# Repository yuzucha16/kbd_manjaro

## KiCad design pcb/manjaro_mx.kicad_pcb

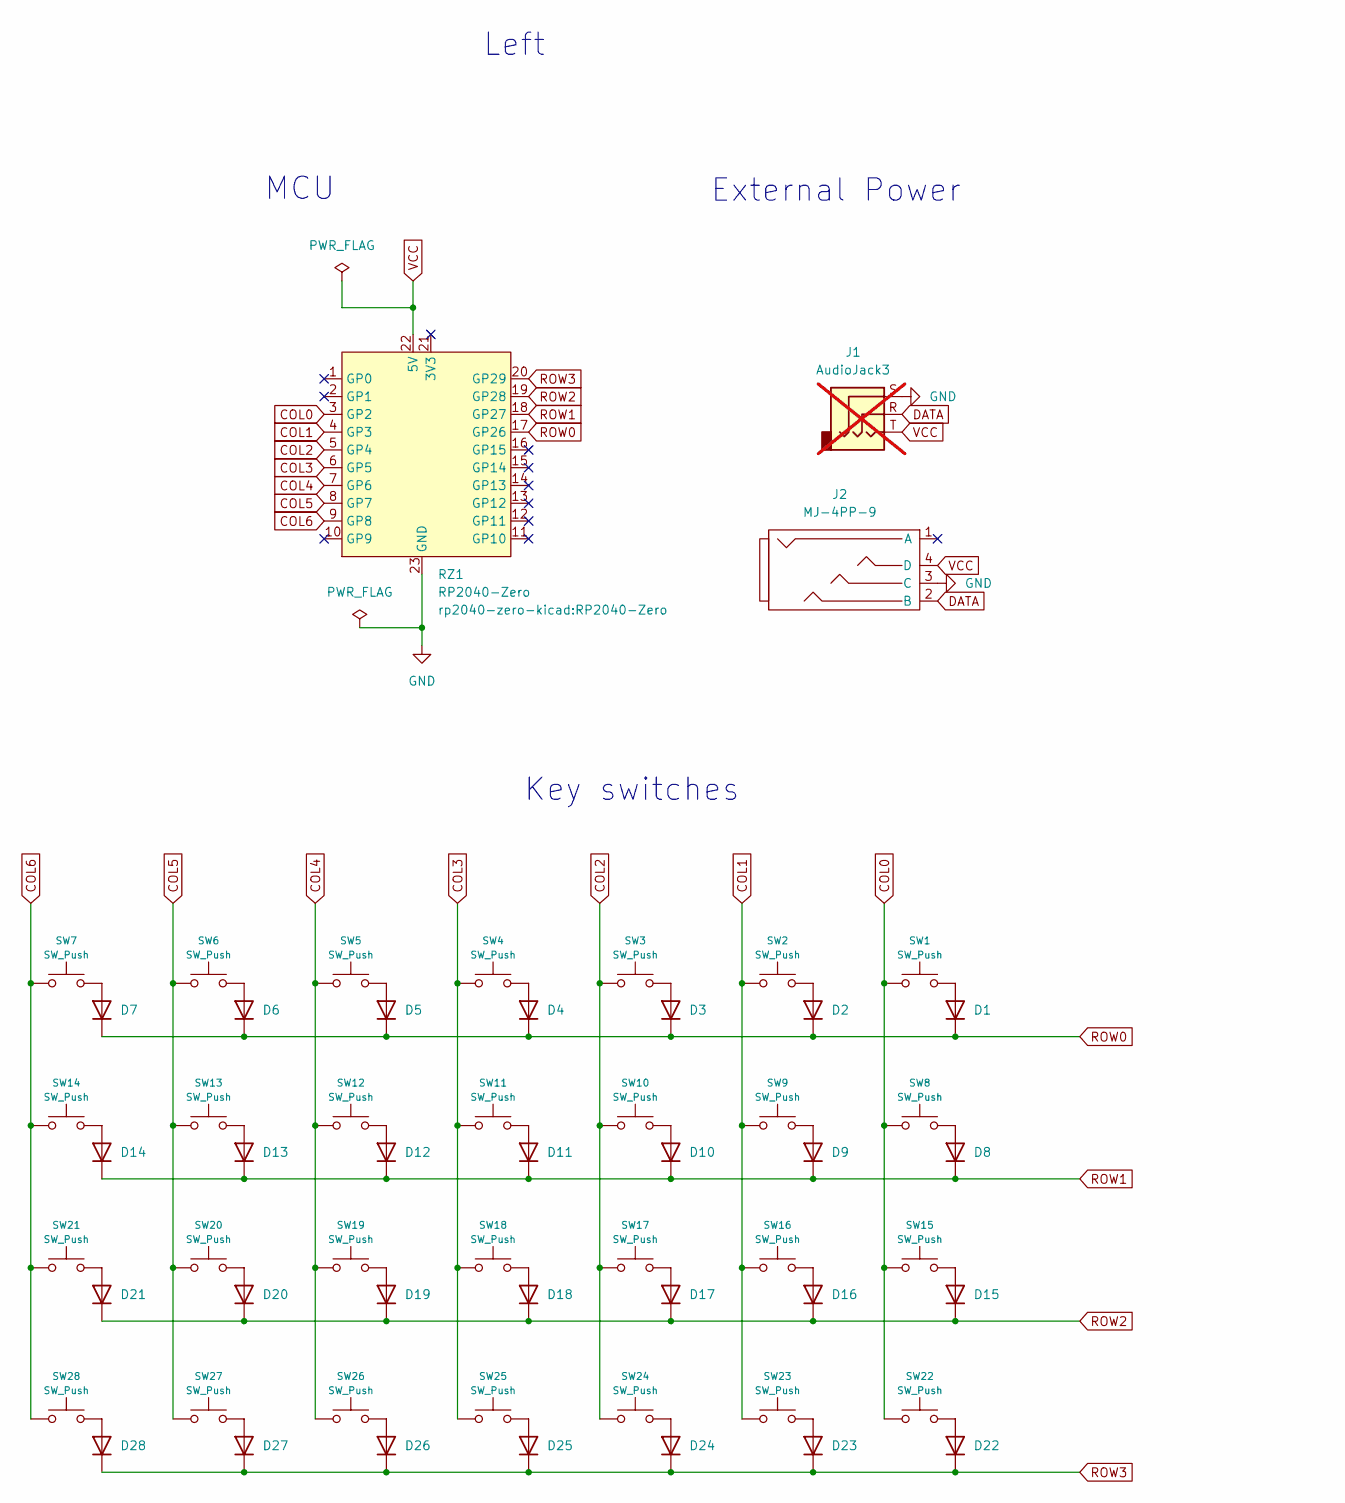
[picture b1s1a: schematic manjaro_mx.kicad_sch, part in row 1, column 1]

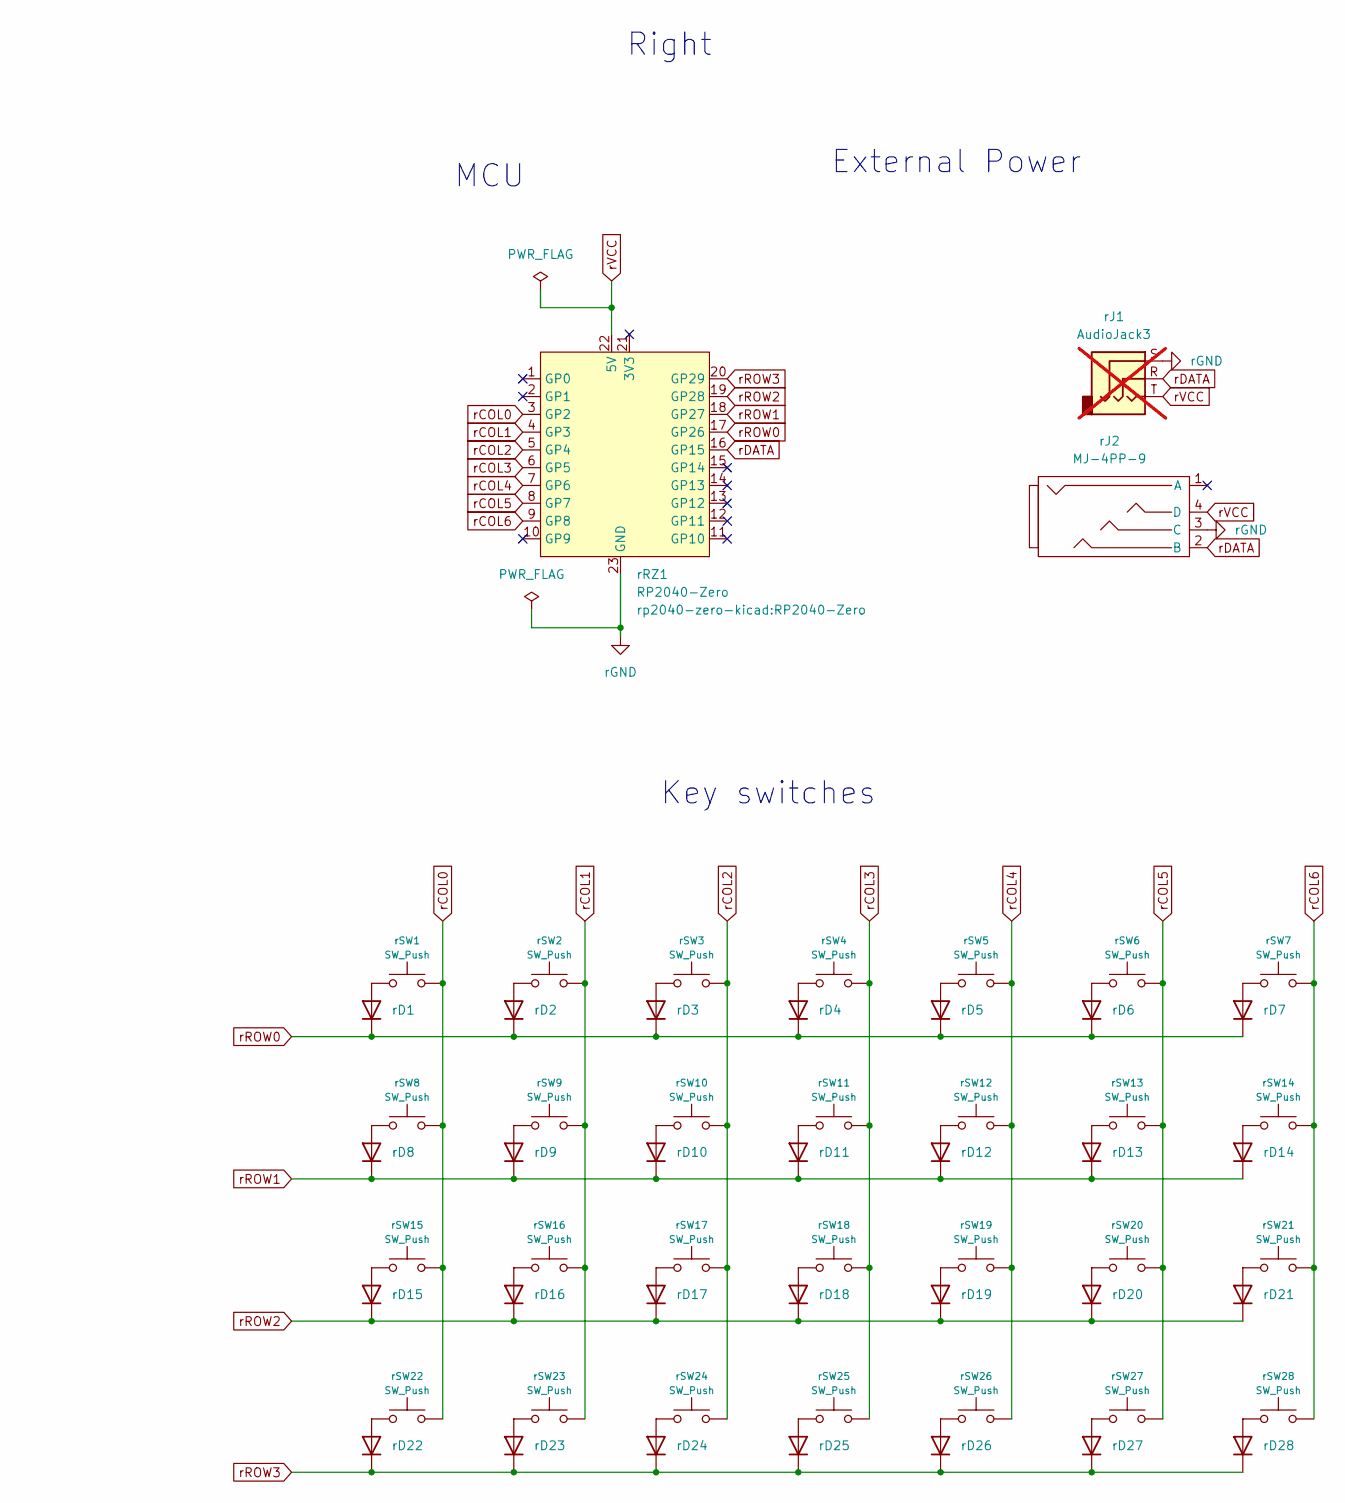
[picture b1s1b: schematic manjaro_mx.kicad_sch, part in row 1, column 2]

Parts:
D1, D2, D3, D4, D5, D6, D7, D8, D9, D10, D11, D12, D13, D14, D15, D16, D17, D18, D19, D20, D21, D22, D23, D24, D25, D26, D27, D28: 1N4148WT; D_SOD-323
J1: AudioJack3; PJ-398A-5A_PJ-399B-6A; not fitted
J2: MJ-4PP-9
RZ1: RP2040-Zero
SW1, SW2, SW3, SW4, SW5, SW6, SW7, SW8, SW9, SW10, SW11, SW12, SW13, SW14, SW15, SW16, SW17, SW18, SW19, SW20, SW21, SW25, SW26, SW27, SW28: SW_Push; keyswitch_cherrymx_hotswap_1u
SW22, SW23, SW24: SW_Push; keyswitch_choc12_hotswap_1u
rD1, rD2, rD3, rD4, rD5, rD6, rD7, rD8, rD9, rD10, rD11, rD12, rD13, rD14, rD15, rD16, rD17, rD18, rD19, rD20, rD21, rD22, rD23, rD24, rD25, rD26, rD27, rD28: 1N4148WT; D_SOD-323
rJ1: AudioJack3; PJ-398A-5A_PJ-399B-6A; not fitted
rJ2: MJ-4PP-9
rRZ1: RP2040-Zero
rSW1, rSW2, rSW3, rSW4, rSW5, rSW6, rSW7, rSW8, rSW9, rSW10, rSW11, rSW12, rSW13, rSW14, rSW15, rSW16, rSW17, rSW18, rSW19, rSW20, rSW21, rSW25, rSW26, rSW27, rSW28: SW_Push; keyswitch_cherrymx_hotswap_1u
rSW22, rSW23, rSW24: SW_Push; keyswitch_choc12_hotswap_1u

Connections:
COL0: RZ1.3 (GP2), SW1.1, SW8.1, SW15.1, SW22.1
COL1: RZ1.4 (GP3), SW2.1, SW9.1, SW16.1, SW23.1
COL2: RZ1.5 (GP4), SW3.1, SW10.1, SW17.1, SW24.1
COL3: RZ1.6 (GP5), SW4.1, SW11.1, SW18.1, SW25.1
COL4: RZ1.7 (GP6), SW5.1, SW12.1, SW19.1, SW26.1
COL5: RZ1.8 (GP7), SW6.1, SW13.1, SW20.1, SW27.1
COL6: RZ1.9 (GP8), SW7.1, SW14.1, SW21.1, SW28.1
DATA: J1.R, J2.2 (B)
GND: J1.S, J2.3 (C), RZ1.23 (GND)
unnamed: D1.2 (A), SW1.2
unnamed: D2.2 (A), SW2.2
unnamed: D3.2 (A), SW3.2
unnamed: D4.2 (A), SW4.2
unnamed: D5.2 (A), SW5.2
unnamed: D6.2 (A), SW6.2
unnamed: D7.2 (A), SW7.2
unnamed: D8.2 (A), SW8.2
unnamed: D9.2 (A), SW9.2
unnamed: D10.2 (A), SW10.2
unnamed: D11.2 (A), SW11.2
unnamed: D12.2 (A), SW12.2
unnamed: D13.2 (A), SW13.2
unnamed: D14.2 (A), SW14.2
unnamed: D15.2 (A), SW15.2
unnamed: D16.2 (A), SW16.2
unnamed: D17.2 (A), SW17.2
unnamed: D18.2 (A), SW18.2
unnamed: D19.2 (A), SW19.2
unnamed: D20.2 (A), SW20.2
unnamed: D21.2 (A), SW21.2
unnamed: D22.2 (A), SW22.2
unnamed: D23.2 (A), SW23.2
unnamed: D24.2 (A), SW24.2
unnamed: D25.2 (A), SW25.2
unnamed: D26.2 (A), SW26.2
unnamed: D27.2 (A), SW27.2
unnamed: D28.2 (A), SW28.2
unnamed: rD1.2 (A), rSW1.1
unnamed: rD2.2 (A), rSW2.1
unnamed: rD3.2 (A), rSW3.1
unnamed: rD4.2 (A), rSW4.1
unnamed: rD5.2 (A), rSW5.1
unnamed: rD6.2 (A), rSW6.1
unnamed: rD7.2 (A), rSW7.1
unnamed: rD8.2 (A), rSW8.1
unnamed: rD9.2 (A), rSW9.1
unnamed: rD10.2 (A), rSW10.1
unnamed: rD11.2 (A), rSW11.1
unnamed: rD12.2 (A), rSW12.1
unnamed: rD13.2 (A), rSW13.1
unnamed: rD14.2 (A), rSW14.1
unnamed: rD15.2 (A), rSW15.1
unnamed: rD16.2 (A), rSW16.1
unnamed: rD17.2 (A), rSW17.1
unnamed: rD18.2 (A), rSW18.1
unnamed: rD19.2 (A), rSW19.1
unnamed: rD20.2 (A), rSW20.1
unnamed: rD21.2 (A), rSW21.1
unnamed: rD22.2 (A), rSW22.1
unnamed: rD23.2 (A), rSW23.1
unnamed: rD24.2 (A), rSW24.1
unnamed: rD25.2 (A), rSW25.1
unnamed: rD26.2 (A), rSW26.1
unnamed: rD27.2 (A), rSW27.1
unnamed: rD28.2 (A), rSW28.1
ROW0: D1.1 (K), D2.1 (K), D3.1 (K), D4.1 (K), D5.1 (K), D6.1 (K), D7.1 (K), RZ1.17 (GP26)
ROW1: D8.1 (K), D9.1 (K), D10.1 (K), D11.1 (K), D12.1 (K), D13.1 (K), D14.1 (K), RZ1.18 (GP27)
ROW2: D15.1 (K), D16.1 (K), D17.1 (K), D18.1 (K), D19.1 (K), D20.1 (K), D21.1 (K), RZ1.19 (GP28)
ROW3: D22.1 (K), D23.1 (K), D24.1 (K), D25.1 (K), D26.1 (K), D27.1 (K), D28.1 (K), RZ1.20 (GP29)
VCC: J1.T, J2.4 (D), RZ1.22 (5V)
rCOL0: rRZ1.3 (GP2), rSW1.2, rSW8.2, rSW15.2, rSW22.2
rCOL1: rRZ1.4 (GP3), rSW2.2, rSW9.2, rSW16.2, rSW23.2
rCOL2: rRZ1.5 (GP4), rSW3.2, rSW10.2, rSW17.2, rSW24.2
rCOL3: rRZ1.6 (GP5), rSW4.2, rSW11.2, rSW18.2, rSW25.2
rCOL4: rRZ1.7 (GP6), rSW5.2, rSW12.2, rSW19.2, rSW26.2
rCOL5: rRZ1.8 (GP7), rSW6.2, rSW13.2, rSW20.2, rSW27.2
rCOL6: rRZ1.9 (GP8), rSW7.2, rSW14.2, rSW21.2, rSW28.2
rDATA: rJ1.R, rJ2.2 (B), rRZ1.16 (GP15)
rGND: rJ1.S, rJ2.3 (C), rRZ1.23 (GND)
rROW0: rD1.1 (K), rD2.1 (K), rD3.1 (K), rD4.1 (K), rD5.1 (K), rD6.1 (K), rD7.1 (K), rRZ1.17 (GP26)
rROW1: rD8.1 (K), rD9.1 (K), rD10.1 (K), rD11.1 (K), rD12.1 (K), rD13.1 (K), rD14.1 (K), rRZ1.18 (GP27)
rROW2: rD15.1 (K), rD16.1 (K), rD17.1 (K), rD18.1 (K), rD19.1 (K), rD20.1 (K), rD21.1 (K), rRZ1.19 (GP28)
rROW3: rD22.1 (K), rD23.1 (K), rD24.1 (K), rD25.1 (K), rD26.1 (K), rD27.1 (K), rD28.1 (K), rRZ1.20 (GP29)
rVCC: rJ1.T, rJ2.4 (D), rRZ1.22 (5V)

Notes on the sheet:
Key switches
MCU
Left
External Power
Right

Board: 2 copper layers, 116 parts (112 on the bottom side), 83 nets, no tracks yet.

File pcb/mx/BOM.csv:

"Designator","Comment","Datasheet","Footprint","Qty","DNP"
"D1,D2,D3,D4,D5,D6,D7,D8,D9,D10,D11,D12,D13,D14,D15,D16,D17,D18,D19,D20,D21,D22,D23,D24,rD1,rD2,rD3,rD4,rD5,rD6,rD7,rD8,rD9,rD10,rD11,rD12,rD13,rD14,rD15,rD16,rD17,rD18,rD19,rD20,rD21","1N4148WT","https://www.diodes.com/assets/Datasheets/ds30396.pdf","Keebio-Parts:D_SOD-323","45",""
"EXSW1,rEXSW1","RotaryEncoder_Switch","~","Keebio-Parts:RotaryEncoder_EC11","2",""
"J2,rJ2","MJ-4PP-9","","MJ-4PP-9:MJ-4PP-9","2",""
"PowerSW1,rPowerSW1","SW_Wuerth_450301014042","https://www.we-online.com/components/products/datasheet/4503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","Button_Switch_THT:SW_Slide-03_Wuerth-WS-SLTV_10x2.5x6.4_P2.54mm","2",""
"rSW1,rSW2,rSW3,rSW4,rSW5,rSW6,rSW7,rSW8,rSW9,rSW10,rSW11,rSW12,rSW13,rSW14,rSW15,rSW16,rSW17,rSW18,rSW19,rSW20,rSW21,SW1,SW2,SW3,SW4,SW5,SW6,SW7,SW8,SW9,SW10,SW11,SW12,SW13,SW14,SW15,SW16,SW17,SW18,SW19,SW20,SW21,SW22,SW23,SW24","SW_Push","~","kbd:keyswitch_cherrymx_hotswap_1u","45",""
"rU1,U1","nice_nano","","nice-nano-kicad:nice_nano","2",""

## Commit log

2024-12-15 [V0] Fixed
2024-12-15 [V0] add jlcpcb files
2024-12-15 [V0] Add TRRS conn for mint right
2024-12-15 [V0] for jlcpcb
2024-12-16 [V0] Add drill & map file for jlcpcb
2025-01-02 Modify key layout
2025-01-02 Modify MCU position
2025-01-02 fixed external line
2025-01-03 fixed keylayout & MCU position
2025-01-03 Fixed v1 layout
2025-01-03 fiexed layout
2025-01-04 Fixed production files
2025-01-04 Add 1key on left hand
2025-01-04 fiexed v1
2025-03-30 [base] layout 7x4 with RP2040 MCU
